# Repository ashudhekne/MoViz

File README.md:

# MoViz
Motion visualization using UWB and IMU

#HardwareFiles
If you want to manufacture your own UWB+IMU+SDCard+Cortex M0 devices, you can start from the harware files.
This is the hardware we used for our experiments. 

#FirmwareFiles
These files are loaded on the hardware. They are Arduino based.

#VisualizationFiles
These files contain the Processing.org files

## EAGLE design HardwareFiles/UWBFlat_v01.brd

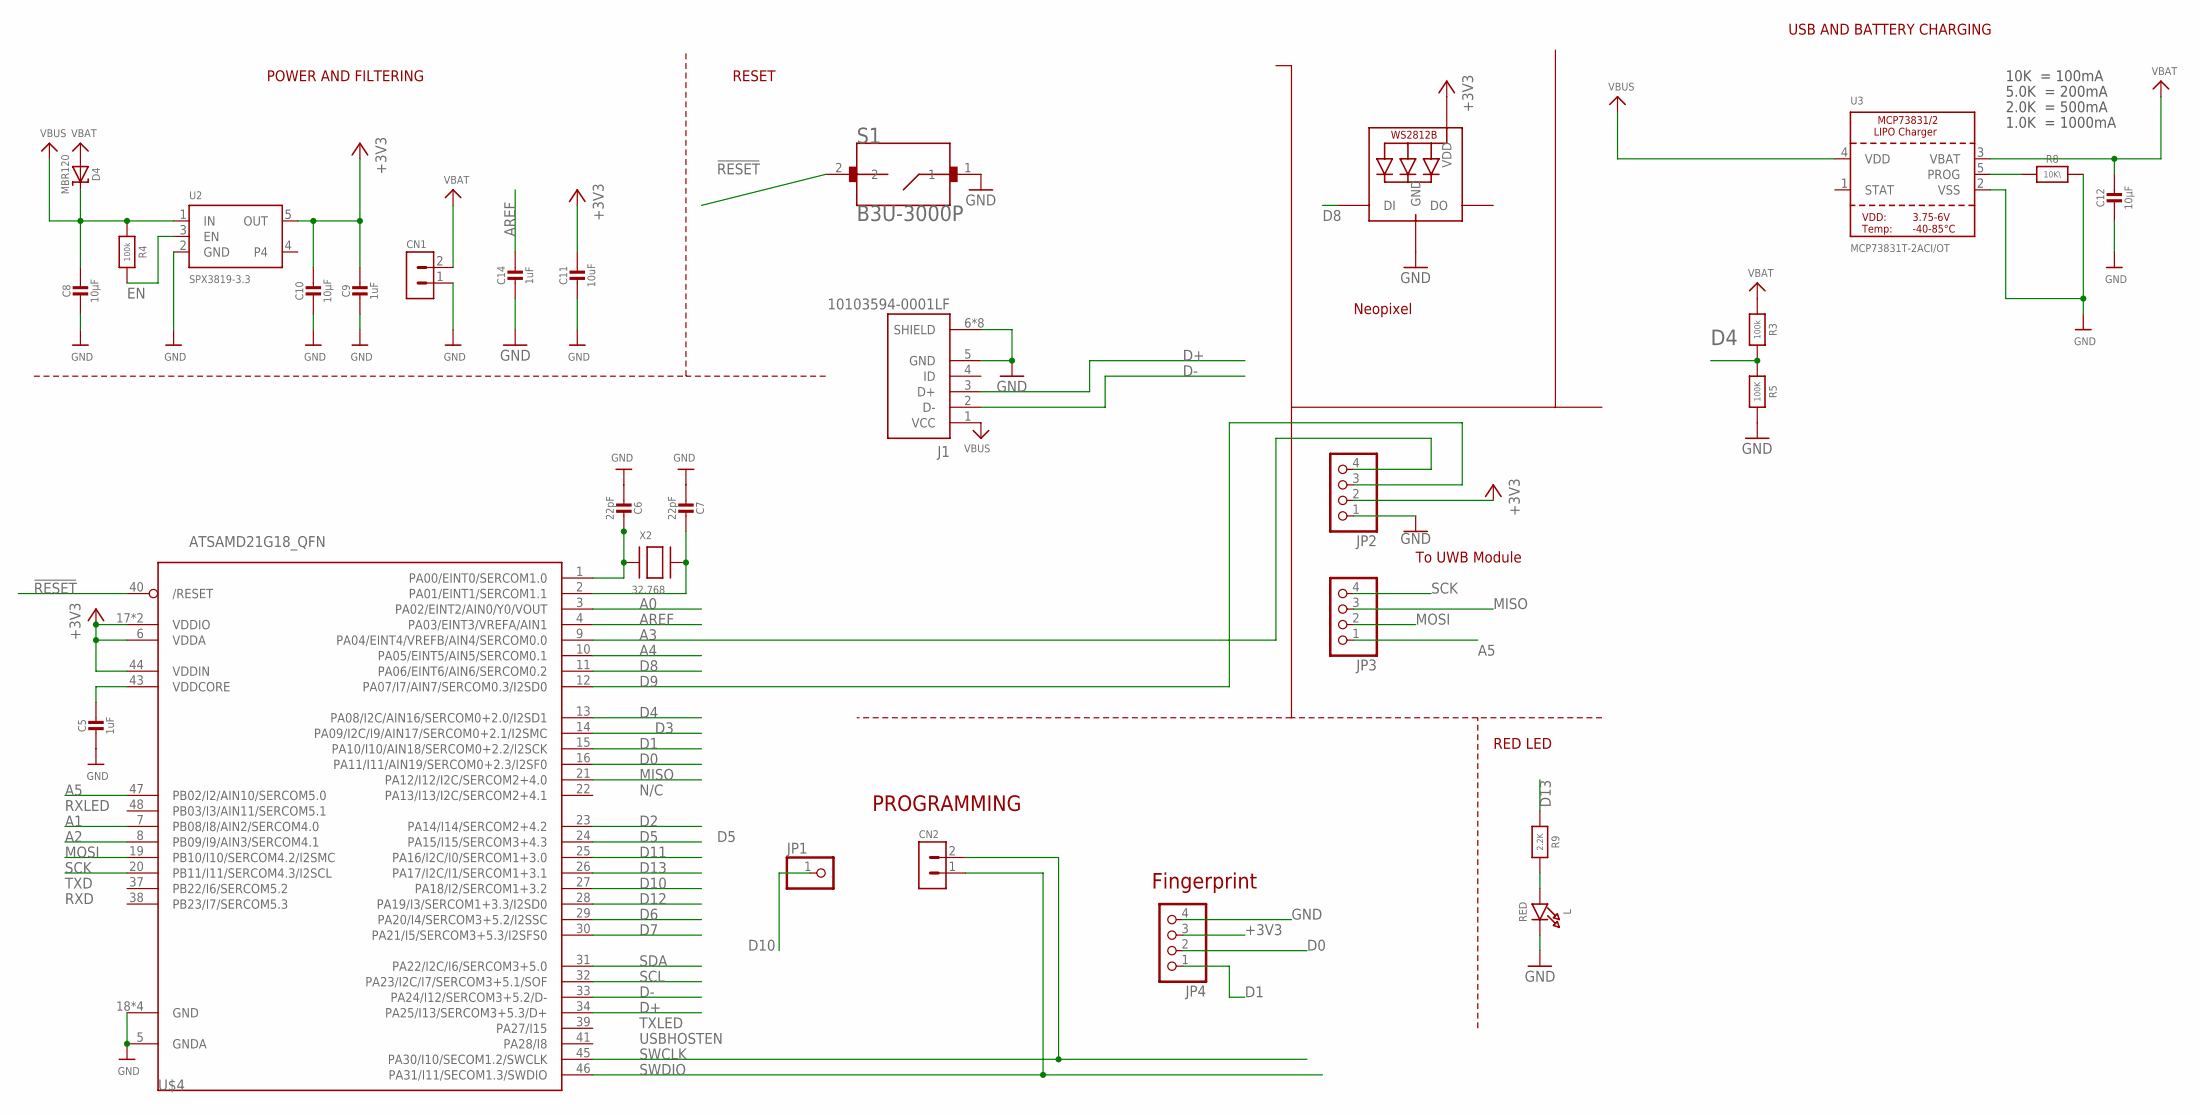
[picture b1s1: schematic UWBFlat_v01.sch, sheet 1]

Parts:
C5, C9, C14: 1uF; 0603-NO
C6, C7: 22pF; 0603-NO
C8, C10, C12: 10µF; 0805-NO
C11: 10uF; 0805-NO
CN1, CN2: HEADER_1X02
D4: MBR120; SOD-123
J1: 10103594-0001LF; AMPHENOL_10103594-0001LF
JP1: PINHD-1X1CB; 1X01-CLEANBIG
JP2, JP3, JP4: HEADER-1X4ROUND; 1X04_ROUND
L: RED; CHIPLED_0805_NOOUTLINE
LED1: WS2812B3535; LED3535
R3, R4: 100k; 0603-NO
R5: 100K; 0603-NO
R8: 10K\; 0603-NO
R9: 2.2K; 0603-NO
S1: B3U-3000P; SW_B3U-3000P
U2: SPX3819-3.3; SOT23-5
U3: MCP73831T-2ACI/OT; SOT23-5
U$4: ATSAMD21G18_QFN; TQFN48_7MM
X2: 32.768; XTAL3215

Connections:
!RESET: S1.2, U$4.40 (/RESET)
+3V3: C9.1, C10.1, C11.1, JP2.2, JP4.3, LED1.2 (VDD), U2.5 (OUT), U$4.6 (VDDA), U$4.17 (VDDIO), U$4.36 (VDDIO), U$4.44 (VDDIN); also elsewhere on the board
A0: U$4.3 (PA02/EINT2/AIN0/Y0/VOUT)
A1: U$4.7 (PB08/I8/AIN2/SERCOM4.0)
A2: U$4.8 (PB09/I9/AIN3/SERCOM4.1)
A3: JP2.4, U$4.9 (PA04/EINT4/VREFB/AIN4/SERCOM0.0); also elsewhere on the board
A4: U$4.10 (PA05/EINT5/AIN5/SERCOM0.1)
A5: JP3.1, U$4.47 (PB02/I2/AIN10/SERCOM5.0); also elsewhere on the board
AREF: C14.1, U$4.4 (PA03/EINT3/VREFA/AIN1)
D0: JP4.2, U$4.16 (PA11/I11/AIN19/SERCOM0+2.3/I2SF0)
D1: JP4.1, U$4.15 (PA10/I10/AIN18/SERCOM0+2.2/I2SCK)
D2: U$4.23 (PA14/I14/SERCOM2+4.2)
D3: U$4.14 (PA09/I2C/I9/AIN17/SERCOM0+2.1/I2SMC)
D4: R3.2, R5.1, U$4.13 (PA08/I2C/AIN16/SERCOM0+2.0/I2SD1)
D5: U$4.24 (PA15/I15/SERCOM3+4.3)
D6: U$4.29 (PA20/I4/SERCOM3+5.2/I2SSC)
D7: U$4.30 (PA21/I5/SERCOM3+5.3/I2SFS0)
D8: LED1.1 (DI), U$4.11 (PA06/EINT6/AIN6/SERCOM0.2)
D9: JP2.3, U$4.12 (PA07/I7/AIN7/SERCOM0.3/I2SD0); also elsewhere on the board
D10: JP1.1, U$4.27 (PA18/I2/SERCOM1+3.2); also elsewhere on the board
D11: U$4.25 (PA16/I2C/I0/SERCOM1+3.0)
D12: U$4.28 (PA19/I3/SERCOM1+3.3/I2SD0)
D13: R9.1, U$4.26 (PA17/I2C/I1/SERCOM1+3.1)
D+: J1.3 (D+), U$4.34 (PA25/I13/SERCOM3+5.3/D+)
D-: J1.2 (D-), U$4.33 (PA24/I12/SERCOM3+5.2/D-)
EN: R4.2, U2.3 (EN)
GND: C5.2, C6.2, C7.2, C8.2, C9.2, C10.2, C11.2, C12.2, C14.2, CN1.1, J1.5 (GND), J1.6 (SHIELD), J1.7 (SHIELD), J1.8 (SHIELD), J1.9 (SHIELD), J1.10 (SHIELD), J1.11 (SHIELD), J1.S1 (SHIELD), J1.S2 (SHIELD), JP2.1, JP4.4, L.C, LED1.4 (GND), R5.2, R8.2, S1.1, U2.2 (GND), U3.2 (VSS), U$4.5 (GNDA), U$4.18 (GND), U$4.35 (GND), U$4.42 (GND), U$4.THERMAL (GND); also elsewhere on the board
MISO: JP3.3, U$4.21 (PA12/I12/I2C/SERCOM2+4.0); also elsewhere on the board
MOSI: JP3.2, U$4.19 (PB10/I10/SERCOM4.2/I2SMC); also elsewhere on the board
unnamed: R8.1, U3.5 (PROG)
unnamed: C6.1, U$4.1 (PA00/EINT0/SERCOM1.0), X2.P$1
unnamed: C7.1, U$4.2 (PA01/EINT1/SERCOM1.1), X2.P$2
unnamed: L.A, R9.2
SCK: JP3.4, U$4.20 (PB11/I11/SERCOM4.3/I2SCL); also elsewhere on the board
SCL: U$4.32 (PA23/I2C/I7/SERCOM3+5.1/SOF); also elsewhere on the board
SDA: U$4.31 (PA22/I2C/I6/SERCOM3+5.0); also elsewhere on the board
SWCLK: CN2.2, U$4.45 (PA30/I10/SECOM1.2/SWCLK)
SWDIO: CN2.1, U$4.46 (PA31/I11/SECOM1.3/SWDIO)
VBAT: C12.1, CN1.2, D4.A, R3.1, U3.3 (VBAT)
VBUS: C8.1, D4.C, J1.1 (VCC), R4.1, U2.1 (IN), U3.4 (VDD)
VDDCORE1: C5.1, U$4.43 (VDDCORE)

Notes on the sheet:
N/C
TXLED
USBHOSTEN
RXLED
TXD
RXD
POWER AND FILTERING
RESET
RED LED
PROGRAMMING
To UWB Module
Neopixel
10K = 100mA
5.0K = 200mA
2.0K = 500mA
1.0K = 1000mA
USB AND BATTERY CHARGING
Fingerprint

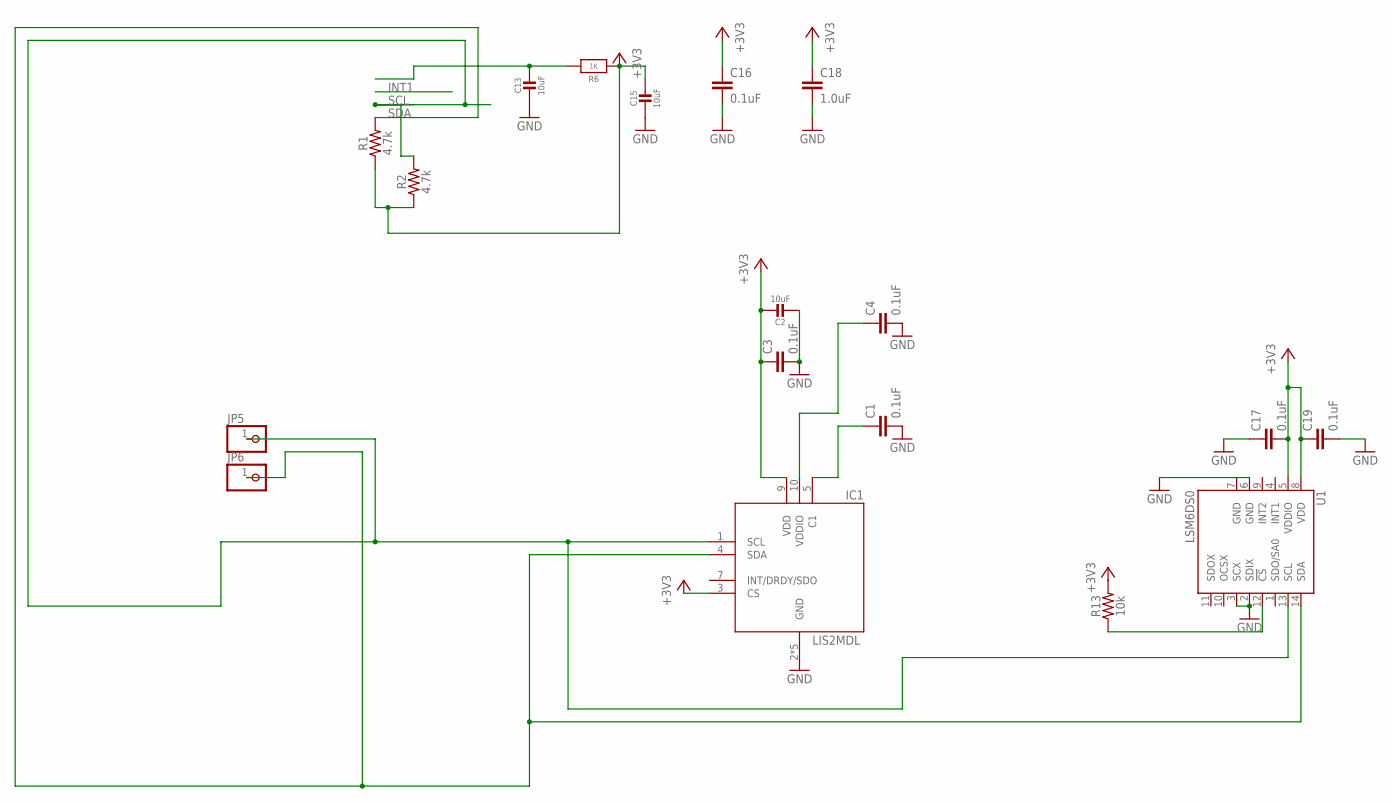
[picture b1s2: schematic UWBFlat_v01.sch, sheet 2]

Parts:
C1, C3, C4, C16, C17, C19: 0.1uF; 0402
C2, C13, C15: 10uF; 0805-NO
C18: 1.0uF; 0603
IC1: LIS2MDL; LGA12_2X2MM
JP5, JP6: PINHD-1X1CB; 1X01-CLEANBIG
R1, R2: 4.7k; 0603
R6: 1K; 0603-NO
R13: 10k; 0603
U1: LSM6DS0; LGA14L

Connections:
+3V3: C2.1, C3.1, C15.1, C16.1, C17.2, C18.1, C19.1, IC1.3 (CS), IC1.9 (VDD), R1.1, R2.1, R6.1, R13.2, U1.5 (VDDIO), U1.8 (VDD); also elsewhere on the board
GND: C1.2, C2.2, C3.2, C4.2, C13.2, C15.2, C16.2, C17.1, C18.2, C19.2, IC1.2 (GND), IC1.6 (GND), IC1.8 (GND), IC1.11 (GND), IC1.12 (GND), U1.2 (SDIX), U1.3 (SCX), U1.6 (GND), U1.7 (GND); also elsewhere on the board
unnamed: C13.1, R6.2
unnamed: C1.1, IC1.5 (C1)
unnamed: C4.1, IC1.10 (VDDIO)
unnamed: R13.1, U1.12 (!CS!)
SCL: IC1.1 (SCL), JP5.1, R2.2, U1.13 (SCL); also elsewhere on the board
SDA: IC1.4 (SDA), JP6.1, R1.2, U1.14 (SDA); also elsewhere on the board

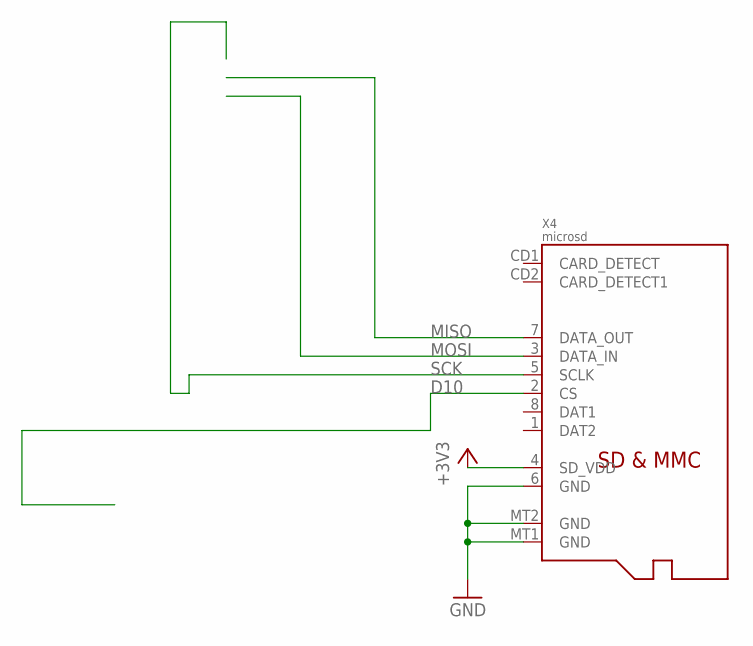
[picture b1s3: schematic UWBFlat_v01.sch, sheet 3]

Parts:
X4: microsd; MICROSD

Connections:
+3V3: X4.4 (SD_VDD); also elsewhere on the board
D10: X4.2 (CS); also elsewhere on the board
GND: X4.6 (GND), X4.MT1 (GND), X4.MT2 (GND); also elsewhere on the board
MISO: X4.7 (DATA_OUT); also elsewhere on the board
MOSI: X4.3 (DATA_IN); also elsewhere on the board
SCK: X4.5 (SCLK); also elsewhere on the board

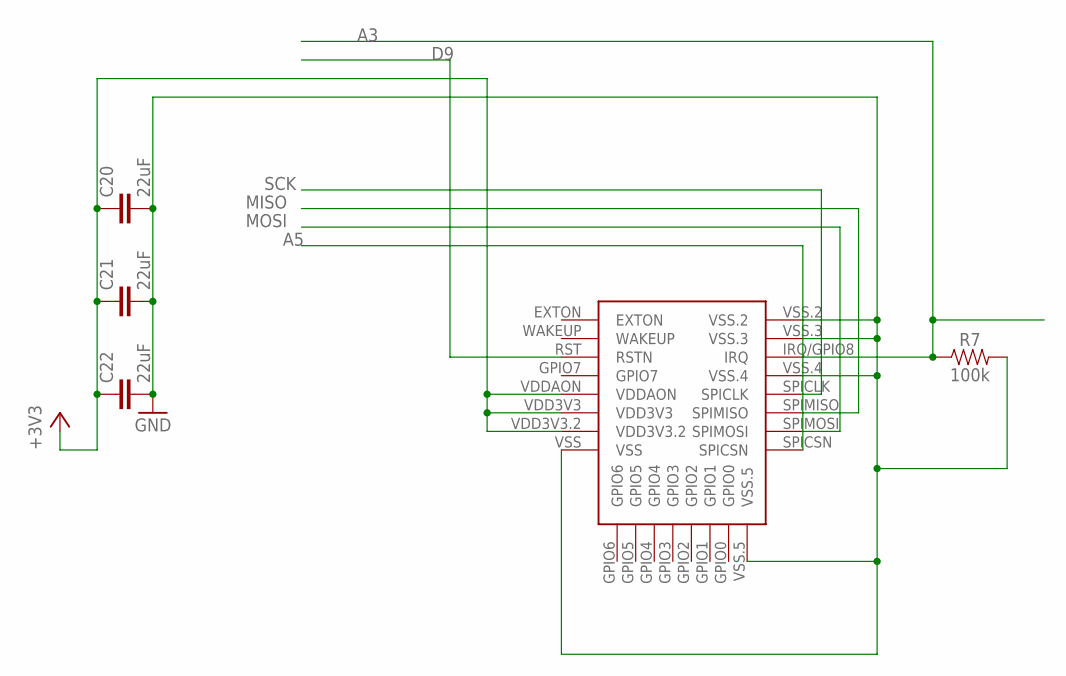
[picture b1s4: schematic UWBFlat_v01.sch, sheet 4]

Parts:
C20, C21, C22: 22uF; 0805
R7: 100k; 0603
U$1: DWM1000

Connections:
+3V3: C20.1, C21.1, C22.1, U$1.VDD3V3, U$1.VDD3V3.2, U$1.VDDAON; also elsewhere on the board
A3: R7.1, U$1.IRQ/GPIO8 (IRQ); also elsewhere on the board
A5: U$1.SPICSN; also elsewhere on the board
D9: U$1.RST (RSTN); also elsewhere on the board
GND: C20.2, C21.2, C22.2, R7.2, U$1.VSS, U$1.VSS.2, U$1.VSS.3, U$1.VSS.4, U$1.VSS.5; also elsewhere on the board
MISO: U$1.SPIMISO; also elsewhere on the board
MOSI: U$1.SPIMOSI; also elsewhere on the board
SCK: U$1.SPICLK; also elsewhere on the board

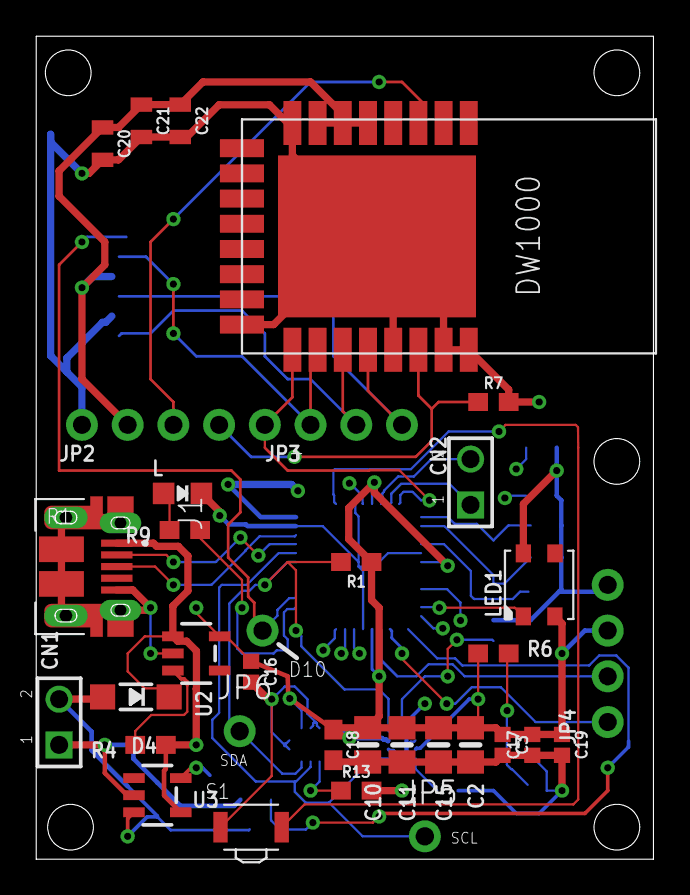
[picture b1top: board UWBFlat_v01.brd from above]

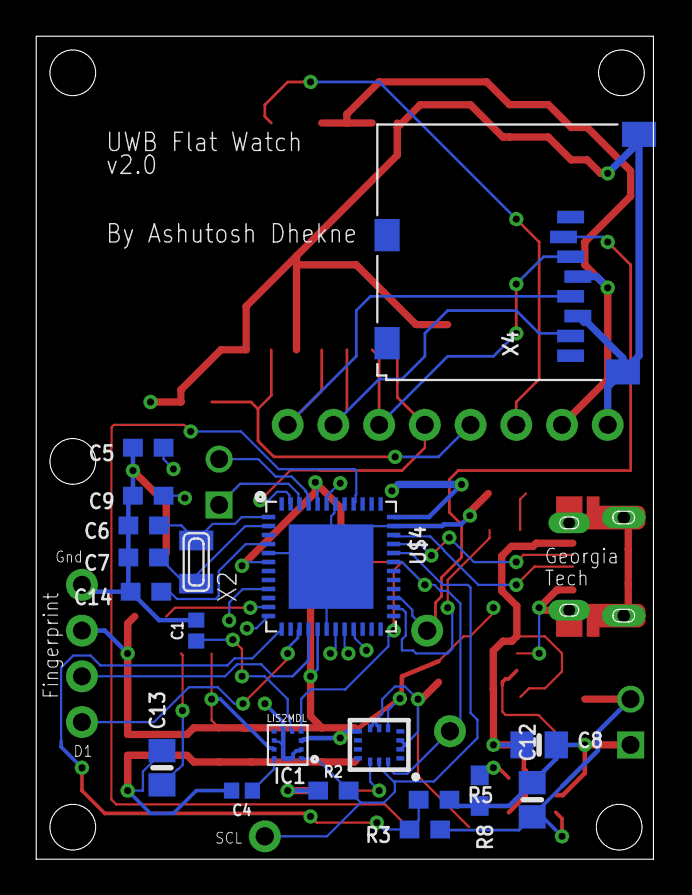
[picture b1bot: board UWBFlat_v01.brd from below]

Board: 4 copper layers, 34.3 x 45.7 mm, 53 parts (19 on the bottom side), 34 nets.

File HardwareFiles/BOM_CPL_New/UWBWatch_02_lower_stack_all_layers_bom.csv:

Comment,Designator,Footprint,LCSC Part #
0.1uF,C3 C16 C17 C19,0402,
1.0uF,C18,0603,
1K,R6,0603-NO,
2.2K,R9,0603-NO,
4.7k,R1,0603,
10k,R13,0603,
10uF,C2 C11 C15,0805-NO,
10µF,C10,0805-NO,
100k,R4,0603-NO,
10103594-0001LF,J1,AMPHENOL_10103594-0001LF,
B3U-3000P,S1,SW_B3U-3000P,
MBR120,D4,SOD-123,
MCP73831T-2ACI/OT,U3,SOT23-5,
RED,L,CHIPLED_0805_NOOUTLINE,
SPX3819-3.3,U2,SOT23-5,
WS2812B3535,LED1,LED3535,
0.1uF,C1 C4,0402,
1uF,C5 C9 C14,0603-NO,
4.7k,R2,0603,
10K\,R8,0603-NO,
10uF,C13,0805-NO,
10µF,C8 C12,0805-NO,
22pF,C6 C7,0603-NO,
32.768,X2,XTAL3215,
100K,R5,0603-NO,
100k,R3,0603-NO,
ATSAMD21G18_QFN,U$4,TQFN48_7MM,
LIS2MDL,IC1,LGA12_2X2MM,
LSM6DS0,U1,LGA14L,

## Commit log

2024-04-23 first_commit
    Setting up for MoViz paper at BodySys 2024
2024-04-23 Adding the bubbles visualization

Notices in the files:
parts and their libraries:
SparkFun-Resistors: Licensing: Creative Commons ShareAlike 4.0 International - https://creativecommons.org/licenses/by-sa/4.0
